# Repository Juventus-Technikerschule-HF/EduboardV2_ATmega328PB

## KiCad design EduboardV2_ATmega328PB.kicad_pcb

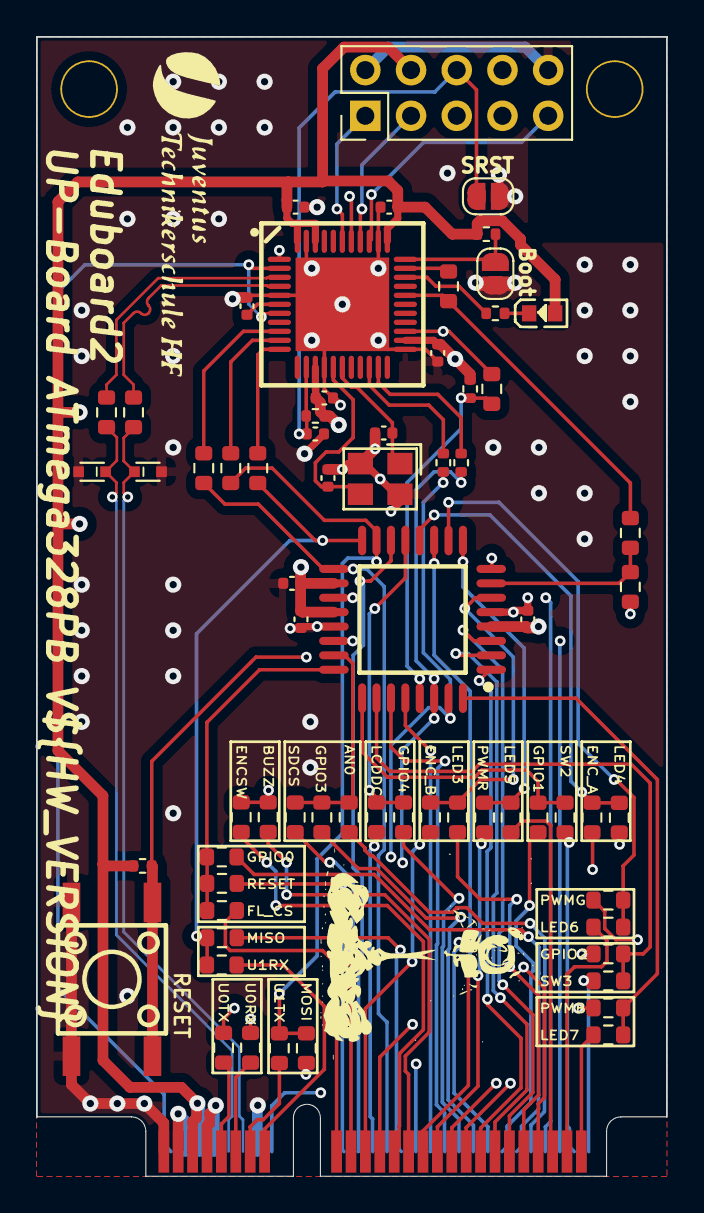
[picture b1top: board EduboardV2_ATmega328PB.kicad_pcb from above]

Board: 4 copper layers, 35.0 x 63.3 mm, 68 parts (0 on the bottom side), 85 nets.

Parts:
C1, C2, C3, C4, C7, C8, C9, C10, C11: 100n; C_0402_1005Metric
C5, C6: 12p; C_0402_1005Metric
D1, D2: LESD5D5.0CT1G; SOD-523_L1.2-W0.8-LS1.6-BI
J1: EduboardV2 PCIE UP Board Connector; mini-PCIe_F1_Full
J2: JTAG_mEDBG; PinHeader_2x05_P2.54mm_Vertical
JP1, JP2: SolderJumper_2_Open; SolderJumper-2_P1.3mm_Open_RoundedPad1.0x1.5mm
LED1: 19-217/BHC-ZL1M2RY/3T; LED0603-FD_BLUE
R1, R2, R3, R4, R5, R6, R7, R8, R9, R10, R11, R12, R13, R14, R15, R16, R17, R18, R19, R20, R21, R22, R23, R24, R25, R26, R27, R30, R31, R32, R33, R34, R37, R38, R40: 0R; R_0603_1608Metric
R28, R29: 1k; R_0402_1005Metric
R35: 10k; R_0402_1005Metric
R36, R45: 3k3; R_0402_1005Metric
R39, R46: 100k; R_0402_1005Metric
R41, R42, R43, R44: 330R; R_0603_1608Metric
SW1: K2-1102SP-C4SC-04; KEY-SMD_4P-L6.0-W6.0-P4.50-LS9.5-BL
U1: ATMEGA328PB-AUR; TQFP-32_L7.0-W7.0-P0.80-LS9.0-BL
U2: ATMEGA32U4-MU; VQFN-44_L7.0-W7.0-P0.50-BL-EP5.2
X1: M16000E067; CRYSTAL-SMD_4P-L3.2-W2.5-BL

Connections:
+3V3: C1.1, C2.1, C3.1, C8.1, C9.2, C10.2, C11.2, J1.5 (3.3V), J1.6 (3.3V), J2.4, LED1.2 (A), R35.1, R39.2, R45.2, R46.2, U1.4 (VCC), U1.18 (AVCC), U1.20 (AREF), U2.14 (VCC), U2.24 (AVCC), U2.34 (VCC), U2.42 (AREF), U2.44 (AVCC)
+5V: J1.3 (5V), J1.4 (5V)
CLK_OUT: R44.2, U2.32 (PC7(ICP3/CLK0/OC4A))
EXT_CLK: R10.1, R44.1, U2.29 (PB5(PCINT5/OC1A/~OC4B/ADC12))
GND: C1.2, C2.2, C3.2, C4.2, C5.2, C6.2, C7.2, C8.2, C9.1, C10.1, C11.1, D1.1, D2.1, J1.1 (GND), J1.7 (GND), J1.8 (GND), J1.14 (GND), J2.2, J2.10, JP1.1 (A), JP2.2 (B), SW1.3, SW1.4, U1.5 (GND), U1.21 (GND), U2.5 (UGnd), U2.15 (GND), U2.23 (GND), U2.35 (GND), U2.43 (GND), U2.45 (EP), X1.2 (GND), X1.4 (GND)
GPIOX0: J1.42 (GPIOX0/AN1/I2S_DOUT), R25.2
GPIOX1: J1.40 (GPIOX1/AN2/I2S_DIN), R30.2
GPIOX2: J1.38 (GPIOX2/AN3/I2S_LRCK), R32.2
GPIOX3: J1.36 (GPIOX3/AN4/I2S_SCLK), R23.2
GPIOX4: J1.34 (GPIOX4/AN5/I2S_MCLK), R11.2
GPIO_AN0: J1.44 (AN0/Pot0), R21.2
GPIO_Buzzer: J1.27 (Buzzer), R2.2
GPIO_FLASH_CS: J1.17 (~FLASH_CS), R26.2
GPIO_LED0: J1.37 (LED0), U1.1 ((OC2B/INT1/PTCXY)PD3)
GPIO_LED1: J1.39 (LED1), U1.2 ((XCK0/T0/PTCXY)PD4)
GPIO_LED2: J1.41 (LED2), U1.3 ((SDA1/ICP4/ACO/PTCXY)PE0)
GPIO_LED3: J1.43 (LED3), R14.1
GPIO_LED4: J1.45 (LED4), R9.2
GPIO_LED5: J1.47 (LED5), R4.2
GPIO_LED6: J1.49 (LED6), R6.2
GPIO_LED7: J1.51 (LED7), R19.1
GPIO_PWM_B: J1.35 (PWM_B), R20.1
GPIO_PWM_G: J1.33 (PWM_G), R5.2
GPIO_PWM_R: J1.31 (PWM_R), R3.2
GPIO_RotEnc_A: J1.23 (RotEnc_A), R7.2
GPIO_RotEnc_B: J1.21 (RotEnc_B), R12.1
GPIO_RotEnc_SW: J1.25 (RotEnc_SW), R1.2
GPIO_SD_CS: J1.19 (~SD_CS), R22.2
GPIO_SW0: J1.46 (SW0), U1.19 (PE2(ADC6/PTCY/ICP3/SS1#))
GPIO_SW1: J1.48 (SW1), U1.22 (PE3(ADC7/PTCY/T3/MOSI1))
GPIO_SW2: J1.50 (SW2), R27.2
GPIO_SW3: J1.52 (SW3), R31.2
GPIO_WS2812_DATA: J1.29 (WS2812_Data), U1.11 ((PTCXY/AIN1)PD7)
LCD_CS: J1.20 (~TFT_CS), U1.14 (~(SS0/OC1B/PTCXY)PB2)
LCD_DC: J1.22 (TFT_DC), R13.2
unnamed: J1.11 (UART0_UP_RX), R34.2
unnamed: J1.9 (UART0_UP_TX), R33.2
unnamed: JP2.1 (A), R46.1, U2.33 (PE2(HWB#))
unnamed: LED1.1 (C), R36.2
unnamed: R7.1, R9.1, U1.12 ((ICP1/CLKO/PTCXY)PB0)
unnamed: R5.1, R6.1, U1.10 ((OC0A/PTCXY/AIN0)PD6)
unnamed: R3.1, R4.1, U1.9 ((OC0B/T1/PTCXY)PD5)
unnamed: R11.1, R13.1, U1.13 ((OC1A/PTCXY)PB1)
unnamed: R12.2, R14.2, U1.6 ((SCL1/T4/PTCXY)PE1)
unnamed: R8.2, R10.2, U1.7 ((XTAL1/TOSC1)PB6)
unnamed: R1.1, R2.1, U1.8 ((XTAL2/TOSC2)PB7)
unnamed: R21.1, R22.1, R23.1, U1.23 (PC0(ADC0/PTCY/MISO1))
unnamed: R24.1, R25.1, R26.1, U1.24 (PC1(ADC1/PTCY/SCK1))
unnamed: R27.1, R30.1, U1.25 (PC2(ADC2/PTCY))
unnamed: R31.1, R32.1, U1.26 (PC3(ADC3/PTCY))
unnamed: R19.2, R20.2, U1.32 (PD2(PTCXY/INT0/OC3B/OC4B))
unnamed: C7.1, U2.6 (UCap)
unnamed: C6.1, U2.17 (XTAL1), X1.1 (OSC1)
unnamed: C5.1, U2.16 (XTAL2), X1.3 (OSC2)
PROG_SPI_MISO: R42.2, U2.11 (PB3(PDO/PCINT3/MISO))
PROG_SPI_MOSI: R43.2, U2.10 (PB2(PDI/PCINT2/MOSI))
PROG_SPI_SCK: R41.2, U2.9 (PB1(PCINT1/SCLK))
PROG_UART_RX: R28.2, U2.20 (PD2(RXD1/INT2))
PROG_UART_TX: R29.2, U2.21 (PD3(TXD1/INT3))
RS485_DE: J1.16 (RS485_DE), R8.1
SCL: J1.30 (SCL), U1.28 (PC5(ADC5/PTCY/SCL0))
SDA: J1.32 (SDA), U1.27 (PC4(ADC4/PTCY/SDA0))
SPI_MISO: J1.26 (SPI_MISO), R17.2
SPI_MOSI: J1.28 (SPI_MOSI), R16.2
SPI_SCK: J1.24 (SPI_SCK), R41.1, U1.17 (PB5(PTCXY/XCK1/SCK0))
STATUS_LED: R36.1, U2.31 (PC6(OC3A/OC4A#))
TCK: J2.1, U2.39 (PF4(ADC4/TCK))
TDI: J2.9, U2.36 (PF7(ADC7/TDI))
TDO: J2.3, U2.37 (PF6(ADC6/TDO))
TMS: J2.5, U2.38 (PF5(ADC5/TMS))
UART0_RX: R29.1, R34.1, U1.30 (PD0(PTCXY/OC3A/RXD0))
UART0_TX: R28.1, R33.1, U1.31 (PD1(PTCXY/OC4A/TXD0))
UART1_RX: J1.15 (UART1_RS485_RX), R18.2
UART1_TX: J1.13 (UART1_RS485_TX), R15.2
UP_SPI_MISO: R17.1, R18.1, R42.1, U1.16 ((MISO0/RXD1/PTCXY)PB4)
UP_SPI_MOSI: R15.1, R16.1, R43.1, U1.15 ((MOSI0/TXD1/OC2A/PTCXY)PB3)
USB_Debug_D+: D2.2, J1.12 (USB_Debug_D+), R38.1
USB_Debug_D-: D1.2, J1.10 (USB_Debug_D-), R37.1
USB_N: R37.2, U2.3 (D-)
USB_P: R38.2, U2.4 (D+)
VBUS: J1.2 (V_USB), U2.2 (UVcc), U2.7 (VBus)
debugWire: R40.2, U2.1 (PE6(INT.6/AIN0)), U2.25 (PD4(ICP1/ADC8))
~General_Reset: J1.18 (~General_Reset), R24.2
~RESET_DW: R35.2, R40.1, R45.1, SW1.1, SW1.2, U1.29 (PC6(RESET#))
~SRST: C4.1, J2.6, JP1.2 (B), R39.1, U2.13 (~RESET)

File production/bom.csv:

Designator,Footprint,Quantity,Value,LCSC Part #
"C1, C10, C11, C2, C3, C4, C7, C8, C9",0402,9,100n,
"C5, C6",0402,2,12p,
"D1, D2",SOD-523_L1.2-W0.8-LS1.6-BI,2,LESD5D5.0CT1G,C383211
"JP1, JP2",SolderJumper-2_P1.3mm_Open_RoundedPad1.0x1.5mm,2,SolderJumper_2_Open,
LED1,LED0603-FD_BLUE,1,19-217/BHC-ZL1M2RY/3T,C72041
"R10, R13, R14, R16, R17, R19, R2, R21, R24, R27, R31, R33, R34, R37, R38, R4, R40, R6, R9",0603,19,0R,
"R28, R29",0402,2,1k,
R35,0402,1,10k,
"R36, R45",0402,2,3k3,
"R39, R46",0402,2,100k,
"R41, R42, R43, R44",0603,4,330R,
SW1,KEY-SMD_4P-L6.0-W6.0-P4.50-LS9.5-BL,1,K2-1102SP-C4SC-04,C127509
U1,TQFP-32_L7.0-W7.0-P0.80-LS9.0-BL,1,ATMEGA328PB-AUR,C461612
U2,VQFN-44_L7.0-W7.0-P0.50-BL-EP5.2,1,ATMEGA32U4-MU,C112161
X1,CRYSTAL-SMD_4P-L3.2-W2.5-BL,1,M16000E067,C279610

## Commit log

2023-04-23 create atmega328 board. Not yet sure if this small microcontroller will be enough for our purposes
2023-04-24 start distribute pins to signals.
2023-04-25 schematic done. layout done aswell. Have to check everything trice
2023-04-25 add .gitignore and delete untracked files
2023-04-25 ready for order first prototype
2023-05-09 got first prototypes. Found some errors. not yet corrected, but marked.
2023-06-25 change mounting hole size to 3mm
2023-06-25 remove voltage regulator and change sense input to 3.3V
2023-06-25 remove USBC Connector, but keep the esd protection
2023-06-25 add VCC to Pin14 of the atmega32u4
2023-06-25 switch miso/mosi from atmega32u4 to atmega328
2023-06-25 switch default routing of j34 miso/uart_rx
2023-06-25 change version to 1.1
2023-06-25 change version to 1.1 again...
2023-06-26 arrange parts and layout v1.1.
2023-06-26 some hexfiles for medbg and stuff...
2023-06-26 create production data
